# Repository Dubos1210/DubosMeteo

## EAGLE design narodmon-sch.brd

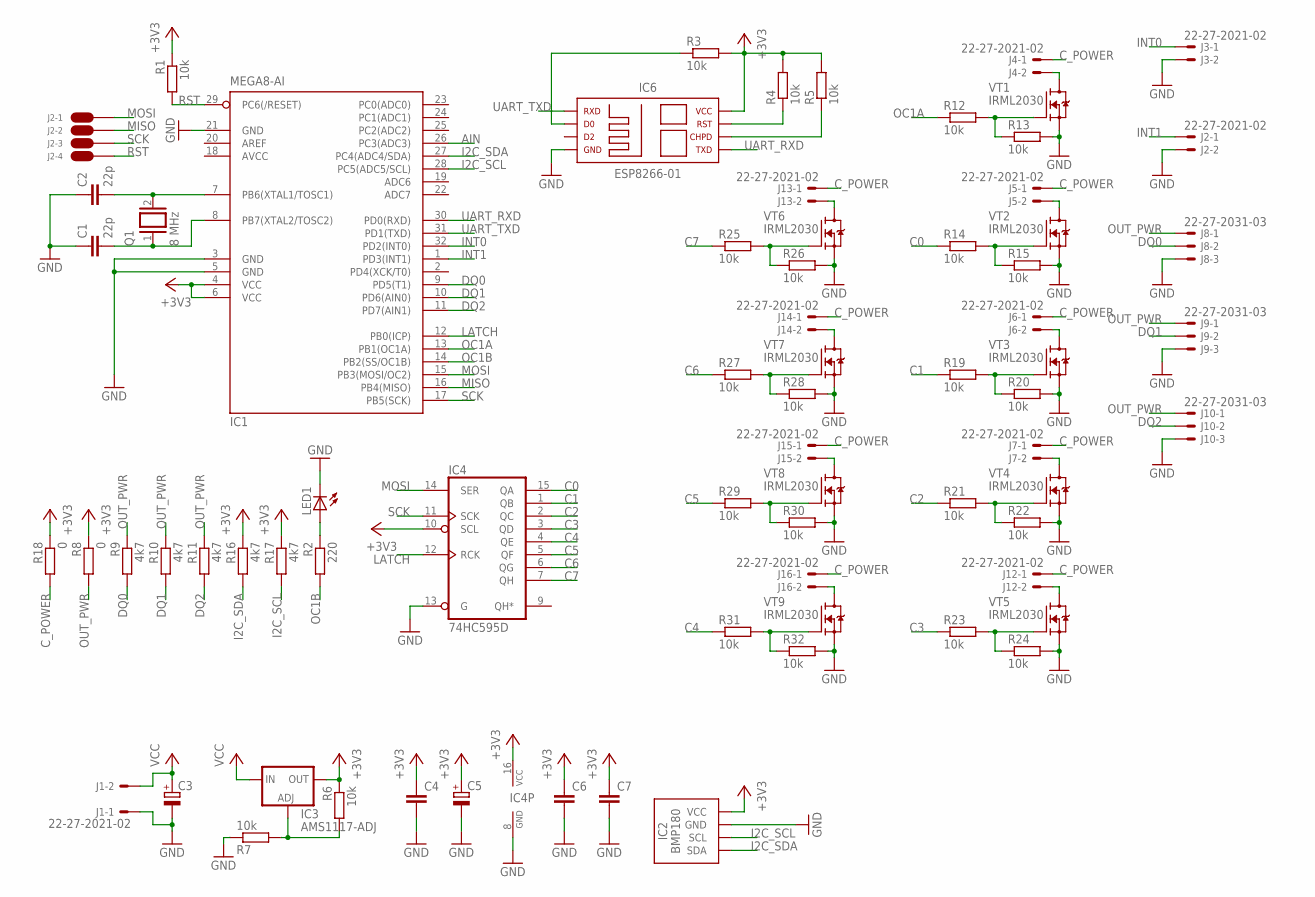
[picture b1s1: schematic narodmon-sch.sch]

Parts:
C1, C2: 22p; C0603
C3: CPOL-EUE3.5-10; E3,5-10
C4, C6, C7: C-EUC0805; C0805
C5: CPOL-EUE2.5-7; E2,5-7
IC1: MEGA8-AI; TQFP32-08
IC2: BMP180C; BMP180-CHIP
IC3: AMS1117-ADJ; SOT223
IC4: 74HC595D; SO16
IC6: ESP-01
J1, J2, J3, J4, J5, J6, J7, J12, J13, J14, J15, J16: 22-27-2021-02; 6410-02
J2-1, J2-2, J2-3, J2-4: W1
J8, J9, J10: 22-27-2031-03; 6410-03
LED1: LED3MM
Q1: 8 MHz; QS
R1, R3, R4, R5, R6, R7, R12, R13, R14, R15, R19, R20, R21, R22, R23, R24, R25, R26, R27, R28, R29, R30, R31, R32: 10k; R0603
R2: 220; R0603
R8: 0; R1206
R9, R10, R11, R16, R17: 4k7; R0603
R18: 0; 0204/7
VT1, VT2, VT3, VT4, VT5, VT6, VT7, VT8, VT9: IRML2030; SOT23

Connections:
+3V3: C4.1, C5.+, C6.1, C7.1, IC1.4 (VCC), IC1.6 (VCC), IC2.P$2 (VCC), IC2.P$3 (VCC), IC3.2 (OUT), IC3.4 (OUT), IC4.10 (SCL), IC4.16 (VCC), IC6.VCC, R1.1, R3.2, R4.2, R5.2, R6.1, R8.1, R16.1, R17.1, R18.1
AIN: IC1.26 (PC3(ADC3))
AVCC: IC1.18 (AVCC)
C0: IC4.15 (QA), R14.1
C1: IC4.1 (QB), R19.1
C2: IC4.2 (QC), R21.1
C3: IC4.3 (QD), R23.1
C4: IC4.4 (QE), R31.1
C5: IC4.5 (QF), R29.1
C6: IC4.6 (QG), R27.1
C7: IC4.7 (QH), R25.1
C_POWER: J4.1, J5.1, J6.1, J7.1, J12.1, J13.1, J14.1, J15.1, J16.1, R18.2
DQ0: IC1.9 (PD5(T1)), J8.2, R9.2
DQ1: IC1.10 (PD6(AIN0)), J9.2, R10.2
DQ2: IC1.11 (PD7(AIN1)), J10.2, R11.2
ESP_CHPD: IC6.CH_PD, R5.1
ESP_G0: IC6.GPIO0, R3.1
ESP_RST: IC6.RST, R4.1
GND: C1.1, C2.1, C3.-, C4.2, C5.-, C6.2, C7.2, IC1.3 (GND), IC1.5 (GND), IC1.21 (GND), IC2.P$7 (GND), IC4.8 (GND), IC4.13 (G), IC6.GND, J1.1, J2.2, J3.2, J8.3, J9.3, J10.3, LED1.K (C), R7.1, R13.2, R15.2, R20.2, R22.2, R24.2, R26.2, R28.2, R30.2, R32.2, VT1.2 (S), VT2.2 (S), VT3.2 (S), VT4.2 (S), VT5.2 (S), VT6.2 (S), VT7.2 (S), VT8.2 (S), VT9.2 (S)
I2C_SCL: IC1.28 (PC5(ADC5/SCL)), IC2.P$5 (SCL), R17.2
I2C_SDA: IC1.27 (PC4(ADC4/SDA)), IC2.P$6 (SDA), R16.2
INT0: IC1.32 (PD2(INT0)), J3.1
INT1: IC1.1 (PD3(INT1)), J2.1
LATCH: IC1.12 (PB0(ICP)), IC4.12 (RCK)
MISO: IC1.16 (PB4(MISO)), J2-2.P$1
MOSI: IC1.15 (PB3(MOSI/OC2)), IC4.14 (SER), J2-1.P$1
unnamed: J4.2, VT1.3 (D)
unnamed: C2.2, IC1.7 (PB6(XTAL1/TOSC1)), Q1.2
unnamed: C1.2, IC1.8 (PB7(XTAL2/TOSC2)), Q1.1
unnamed: R12.2, R13.1, VT1.1 (G)
unnamed: R14.2, R15.1, VT2.1 (G)
unnamed: LED1.A, R2.1
unnamed: J5.2, VT2.3 (D)
unnamed: R19.2, R20.1, VT3.1 (G)
unnamed: J6.2, VT3.3 (D)
unnamed: R21.2, R22.1, VT4.1 (G)
unnamed: J7.2, VT4.3 (D)
unnamed: R23.2, R24.1, VT5.1 (G)
unnamed: J12.2, VT5.3 (D)
unnamed: R25.2, R26.1, VT6.1 (G)
unnamed: J13.2, VT6.3 (D)
unnamed: R27.2, R28.1, VT7.1 (G)
unnamed: J14.2, VT7.3 (D)
unnamed: R29.2, R30.1, VT8.1 (G)
unnamed: J15.2, VT8.3 (D)
unnamed: R31.2, R32.1, VT9.1 (G)
unnamed: J16.2, VT9.3 (D)
unnamed: IC3.1 (ADJ), R6.2, R7.2
OC1A: IC1.13 (PB1(OC1A)), R12.1
OC1B: IC1.14 (PB2(SS/OC1B)), R2.2
OUT_PWR: J8.1, J9.1, J10.1, R8.2, R9.1, R10.1, R11.1
RST: IC1.29 (PC6(/RESET)), J2-4.P$1, R1.2
SCK: IC1.17 (PB5(SCK)), IC4.11 (SCK), J2-3.P$1
UART_RXD: IC1.30 (PD0(RXD)), IC6.TXD
UART_TXD: IC1.31 (PD1(TXD)), IC6.RXC (RXD)
VCC: C3.+, IC3.3 (IN), J1.2

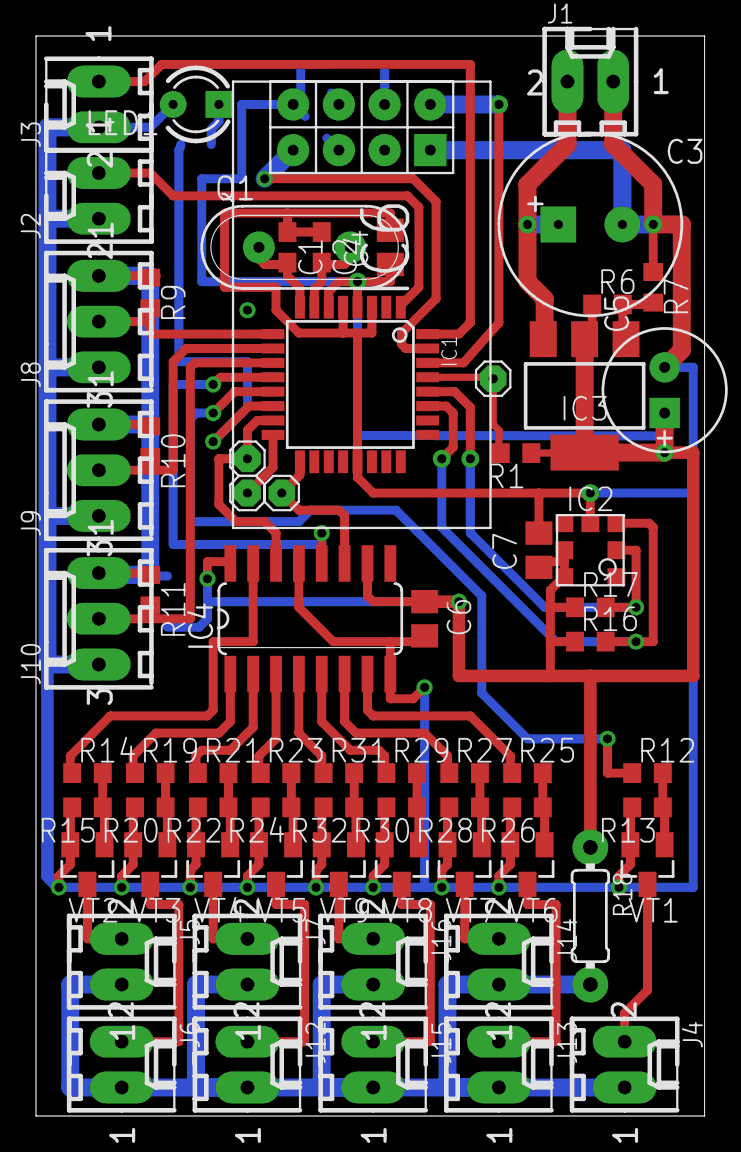
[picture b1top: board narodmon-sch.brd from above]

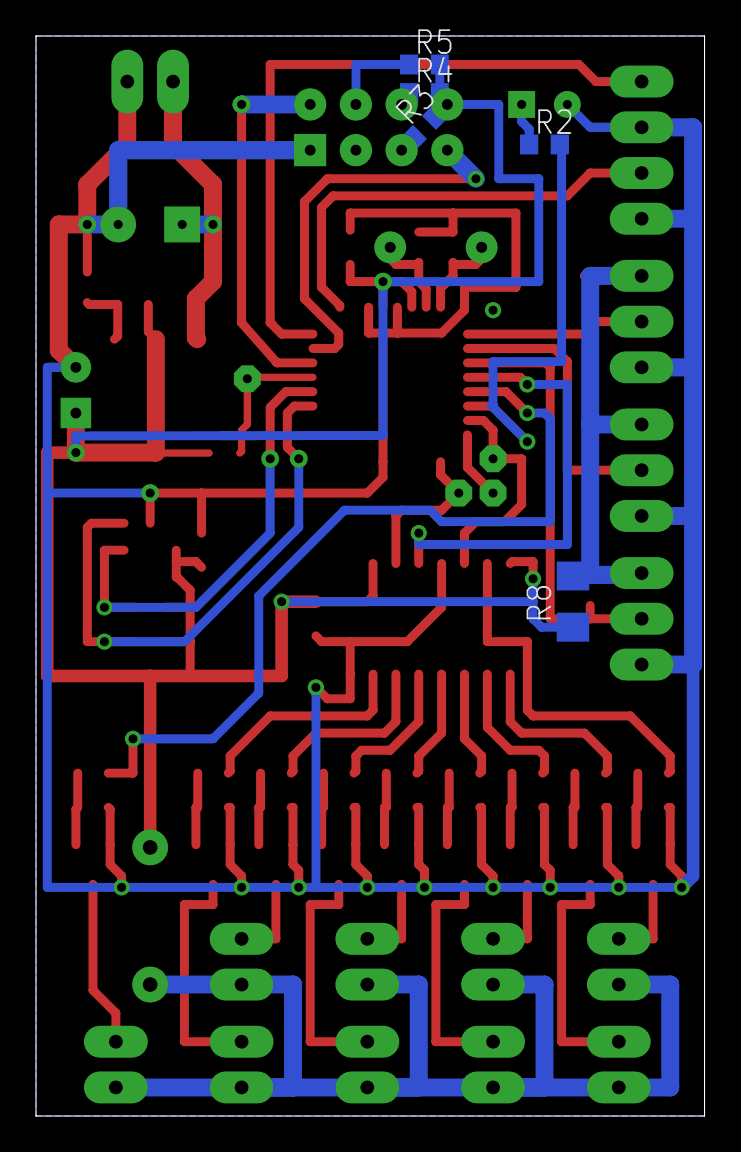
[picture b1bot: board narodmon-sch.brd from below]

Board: 2 copper layers, 37.1 x 60.0 mm, 74 parts (5 on the bottom side), 54 nets.
